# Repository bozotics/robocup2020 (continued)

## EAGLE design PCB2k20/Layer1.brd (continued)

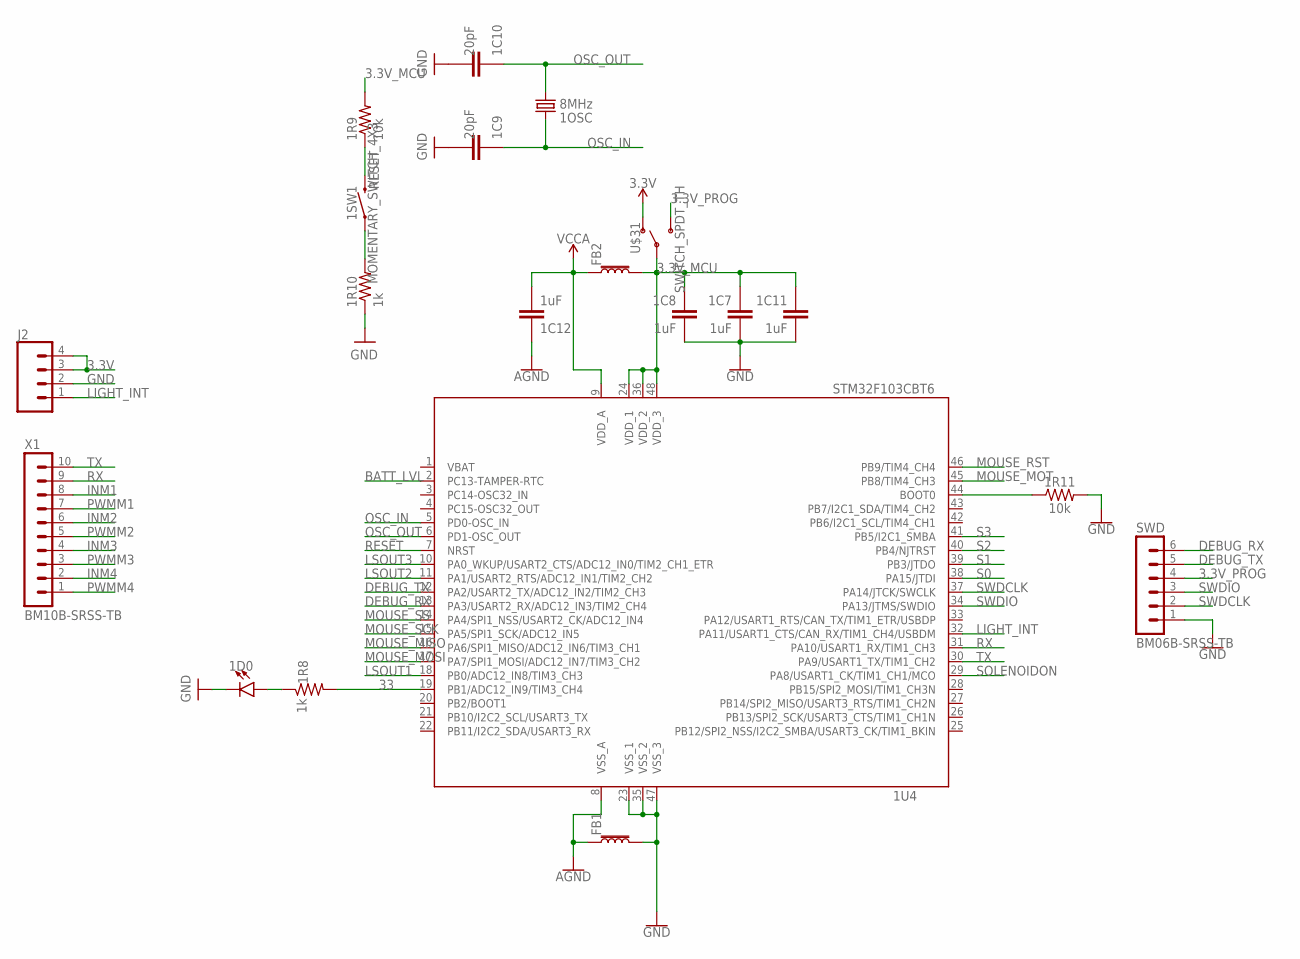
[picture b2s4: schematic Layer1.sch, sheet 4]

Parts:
1C7, 1C8, 1C11, 1C12: 1uF; C0603
1C9, 1C10: 20pF; C0603
1D0: BLUE; LED-0603
1OSC: 8MHz; CRYSTAL-SMD-5X3.2-2PAD
1R8, 1R10: 1k; R0603
1R9, 1R11: 10k; R0603
1SW1: MOMENTARY_SWITCH_4X3
1U4: STM32F103CBT6; LQFP48
FB1, FB2: FERRITE_BEAD; R0603
J2: CONN_04LOCK; 1X04_LOCK
SWD: BM06B-SRSS-TB
U$31: SWITCH_SPDT_TH; SWITCH_SPDT_PTH_11.6X4.0MM_LOCK
X1: BM10B-SRSS-TB

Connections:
3.3V: J2.3, J2.4, U$31.1 (O); also elsewhere on the board
3.3V_MCU: 1C7.1, 1C8.1, 1C11.1, 1R9.2, 1U4.24 (VDD_1), 1U4.36 (VDD_2), 1U4.48 (VDD_3), FB2.2, U$31.2
3.3V_PROG: SWD.4, U$31.3 (S)
33: 1R8.2, 1U4.19 (PB1/ADC12_IN9/TIM3_CH4)
AGND: 1C12.1, 1U4.8 (VSS_A), FB1.1; also elsewhere on the board
BATT_LVL: 1U4.2 (PC13-TAMPER-RTC); also elsewhere on the board
DEBUG_RX: 1U4.13 (PA3/USART2_RX/ADC12_IN3/TIM2_CH4), SWD.6
DEBUG_TX: 1U4.12 (PA2/USART2_TX/ADC12_IN2/TIM2_CH3), SWD.5
GND: 1C7.2, 1C8.2, 1C9.2, 1C10.2, 1C11.2, 1D0.C, 1R10.1, 1R11.2, 1U4.23 (VSS_1), 1U4.35 (VSS_2), 1U4.47 (VSS_3), FB1.2, J2.2, SWD.1; also elsewhere on the board
INM1: X1.8; also elsewhere on the board
INM2: X1.6; also elsewhere on the board
INM3: X1.4; also elsewhere on the board
INM4: X1.2; also elsewhere on the board
LIGHT_INT: 1U4.32 (PA11/USART1_CTS/CAN_RX/TIM1_CH4/USBDM), J2.1
LSOUT1: 1U4.18 (PB0/ADC12_IN8/TIM3_CH3); also elsewhere on the board
LSOUT2: 1U4.11 (PA1/USART2_RTS/ADC12_IN1/TIM2_CH2); also elsewhere on the board
LSOUT3: 1U4.10 (PA0_WKUP/USART2_CTS/ADC12_IN0/TIM2_CH1_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); also elsewhere on the board
MOUSE_MISO: 1U4.16 (PA6/SPI1_MISO/ADC12_IN6/TIM3_CH1); also elsewhere on the board
MOUSE_MOSI: 1U4.17 (PA7/SPI1_MOSI/ADC12_IN7/TIM3_CH2); also elsewhere on the board
MOUSE_MOT: 1U4.45 (PB8/TIM4_CH3); also elsewhere on the board
MOUSE_RST: 1U4.46 (PB9/TIM4_CH4); also elsewhere on the board
MOUSE_SCK: 1U4.15 (PA5/SPI1_SCK/ADC12_IN5); also elsewhere on the board
MOUSE_SS: 1U4.14 (PA4/SPI1_NSS/USART2_CK/ADC12_IN4); also elsewhere on the board
unnamed: 1R10.2, 1SW1.P$1 (1)
unnamed: 1D0.A, 1R8.1
unnamed: 1R11.1, 1U4.44 (BOOT0)
OSC_IN: 1C9.1, 1OSC.P$2 (2), 1U4.5 (PD0-OSC_IN)
OSC_OUT: 1C10.1, 1OSC.P$1 (1), 1U4.6 (PD1-OSC_OUT)
PWMM1: X1.7; also elsewhere on the board
PWMM2: X1.5; also elsewhere on the board
PWMM3: X1.3; also elsewhere on the board
PWMM4: X1.1; also elsewhere on the board
RESET: 1R9.1, 1SW1.P$2 (2), 1U4.7 (NRST)
RX: 1U4.31 (PA10/USART1_RX/TIM1_CH3), X1.9
S0: 1U4.38 (PA15/JTDI); also elsewhere on the board
S1: 1U4.39 (PB3/JTDO); also elsewhere on the board
S2: 1U4.40 (PB4/NJTRST); also elsewhere on the board
S3: 1U4.41 (PB5/I2C1_SMBA); also elsewhere on the board
SOLENOIDON: 1U4.29 (PA8/USART1_CK/TIM1_CH1/MCO); also elsewhere on the board
SWDCLK: 1U4.37 (PA14/JTCK/SWCLK), SWD.2
SWDIO: 1U4.34 (PA13/JTMS/SWDIO), SWD.3
TX: 1U4.30 (PA9/USART1_TX/TIM1_CH2), X1.10
VBAT: 1U4.1 (VBAT)
VCCA: 1C12.2, 1U4.9 (VDD_A), FB2.1; also elsewhere on the board

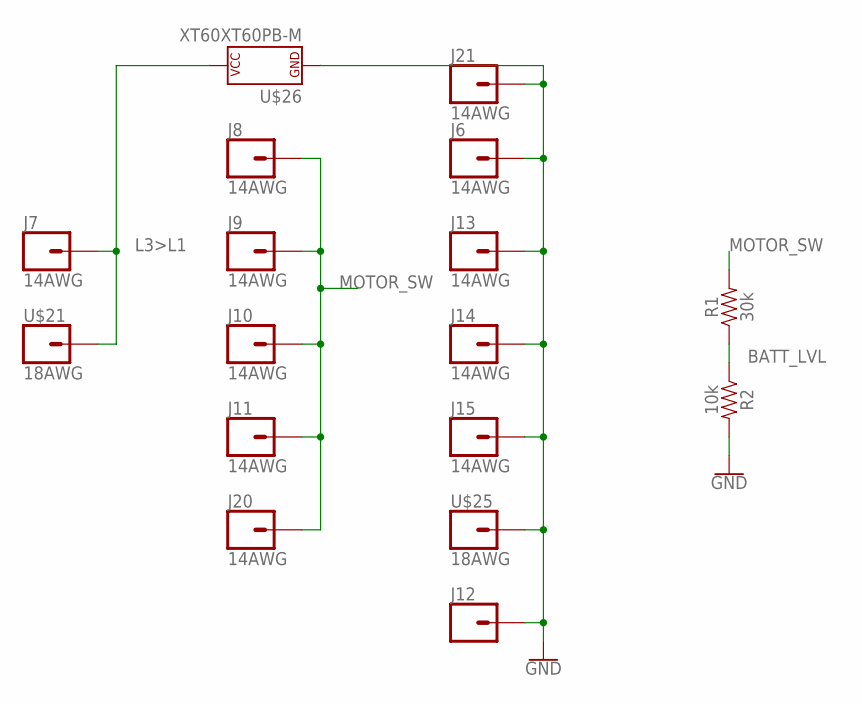
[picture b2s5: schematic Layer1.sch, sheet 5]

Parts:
J6, J7, J8, J9, J10, J11, J13, J14, J15, J20, J21: 14AWG
J12: CONN_01; 1X01
R1: 30k; R0603
R2: 10k; R0603
U$21, U$25: 18AWG
U$26: XT60XT60PB-M; XT60PB-M

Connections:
BATT_LVL: R1.1, R2.1; also elsewhere on the board
GND: J6.P$1, J12.1, J13.P$1, J14.P$1, J15.P$1, J21.P$1, R2.2, U$25.P$1, U$26.- (P$V-); also elsewhere on the board
L3>L1: J7.P$1, U$21.P$1, U$26.+ (P$V+)
MOTOR_SW: J8.P$1, J9.P$1, J10.P$1, J11.P$1, J20.P$1, R1.2

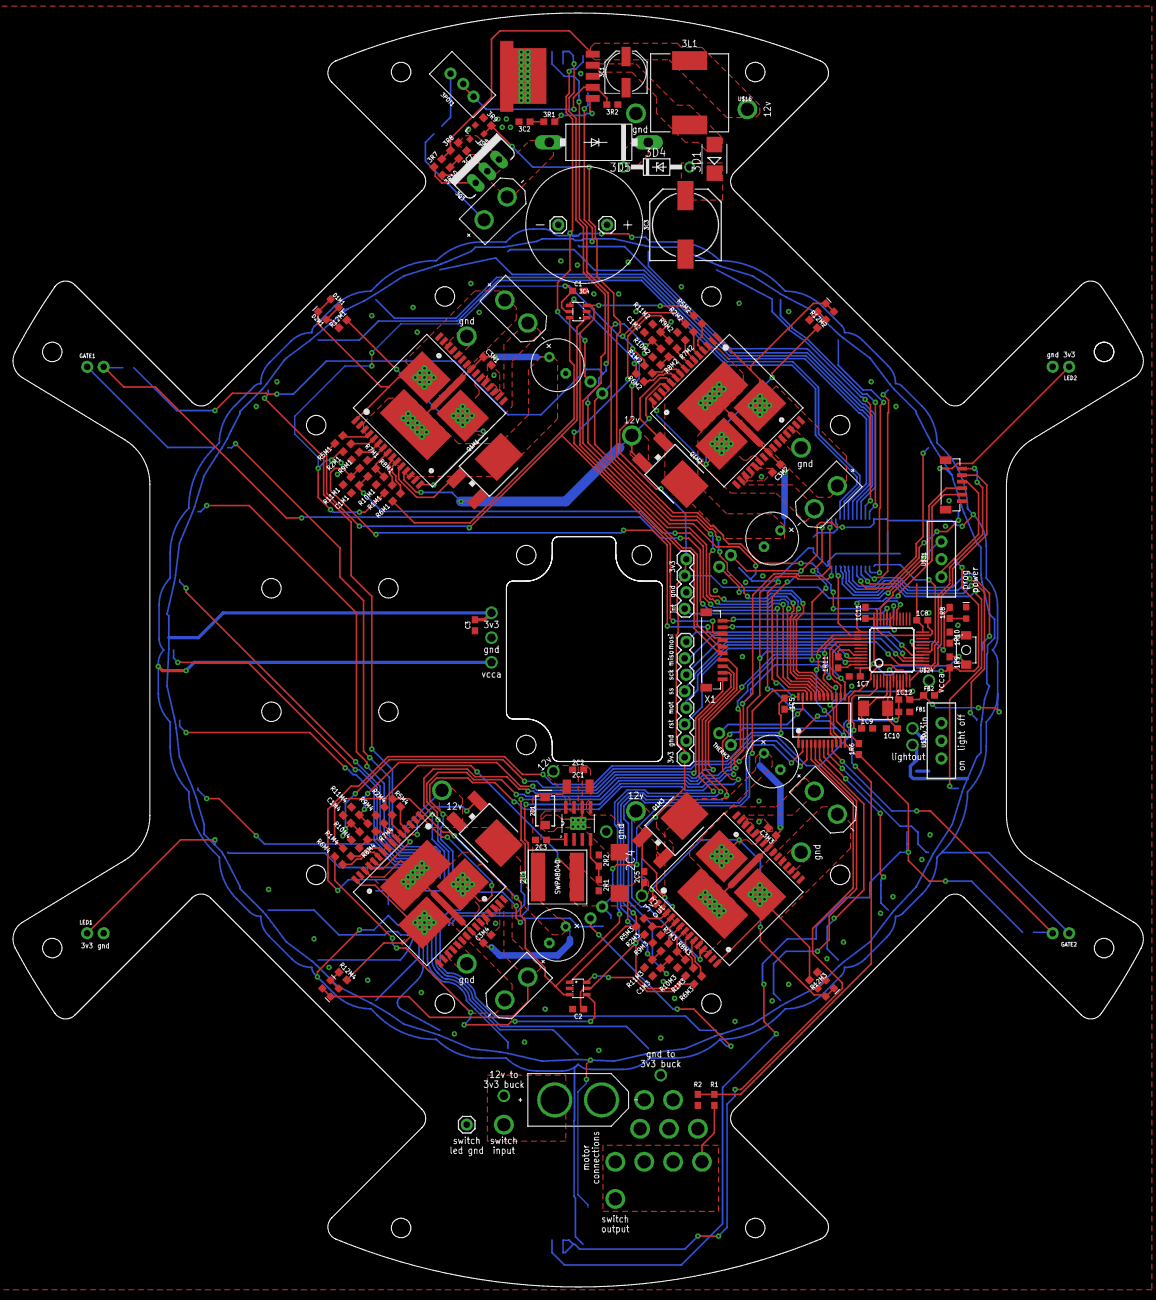
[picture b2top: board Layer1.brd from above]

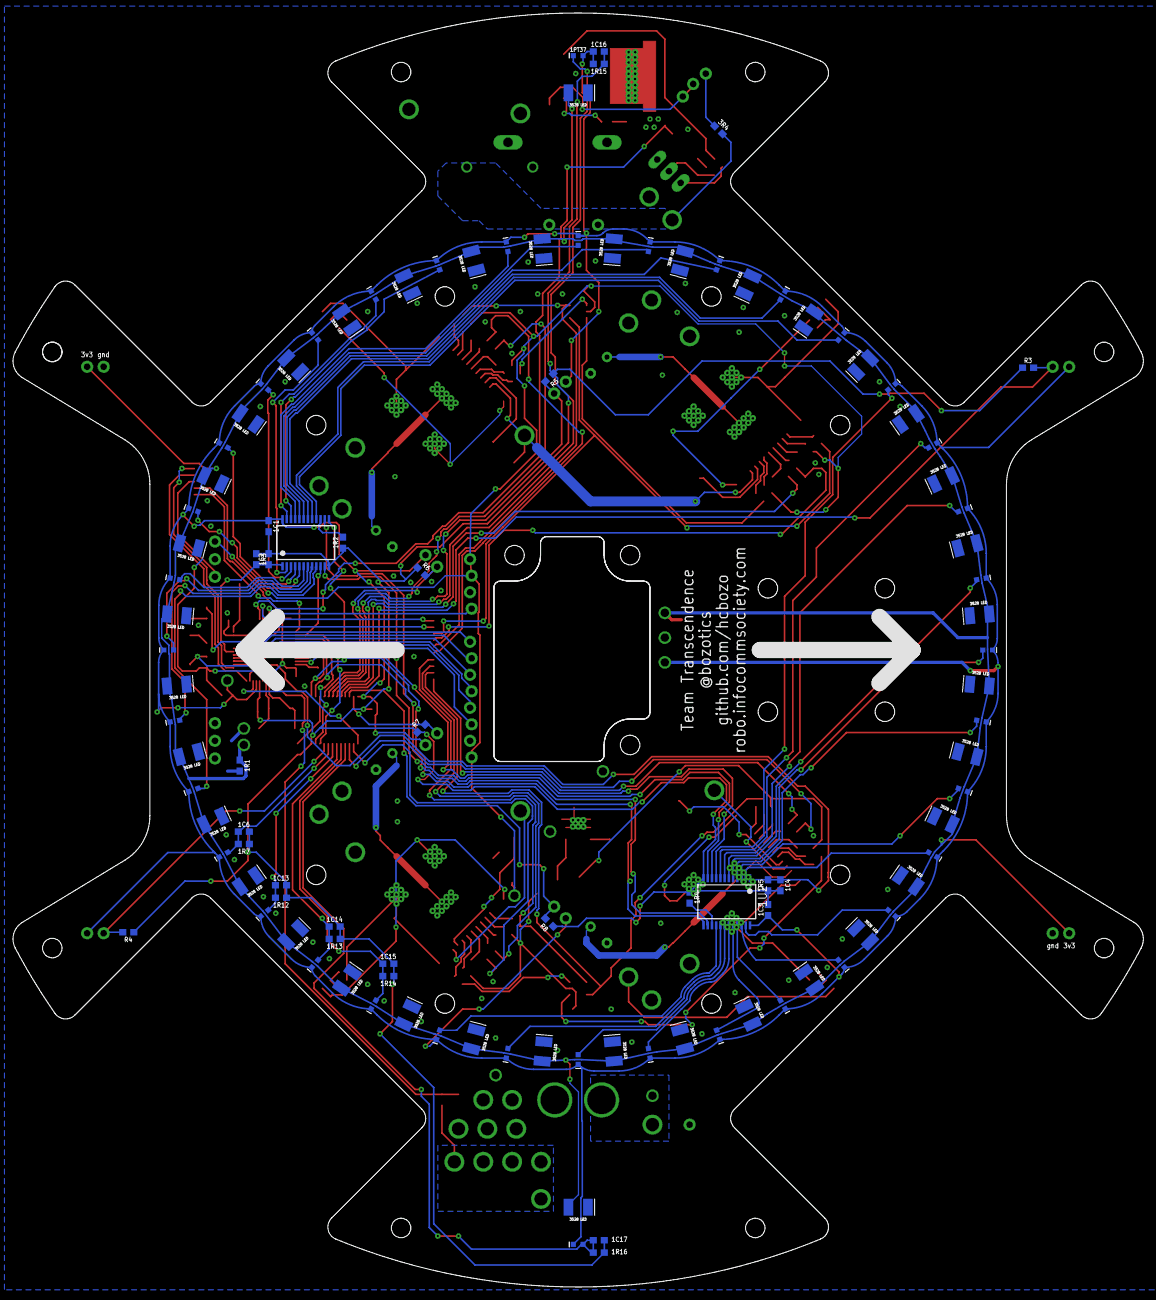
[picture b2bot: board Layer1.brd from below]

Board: 2 copper layers, 173.9 x 196.0 mm, 281 parts (106 on the bottom side), 170 nets.

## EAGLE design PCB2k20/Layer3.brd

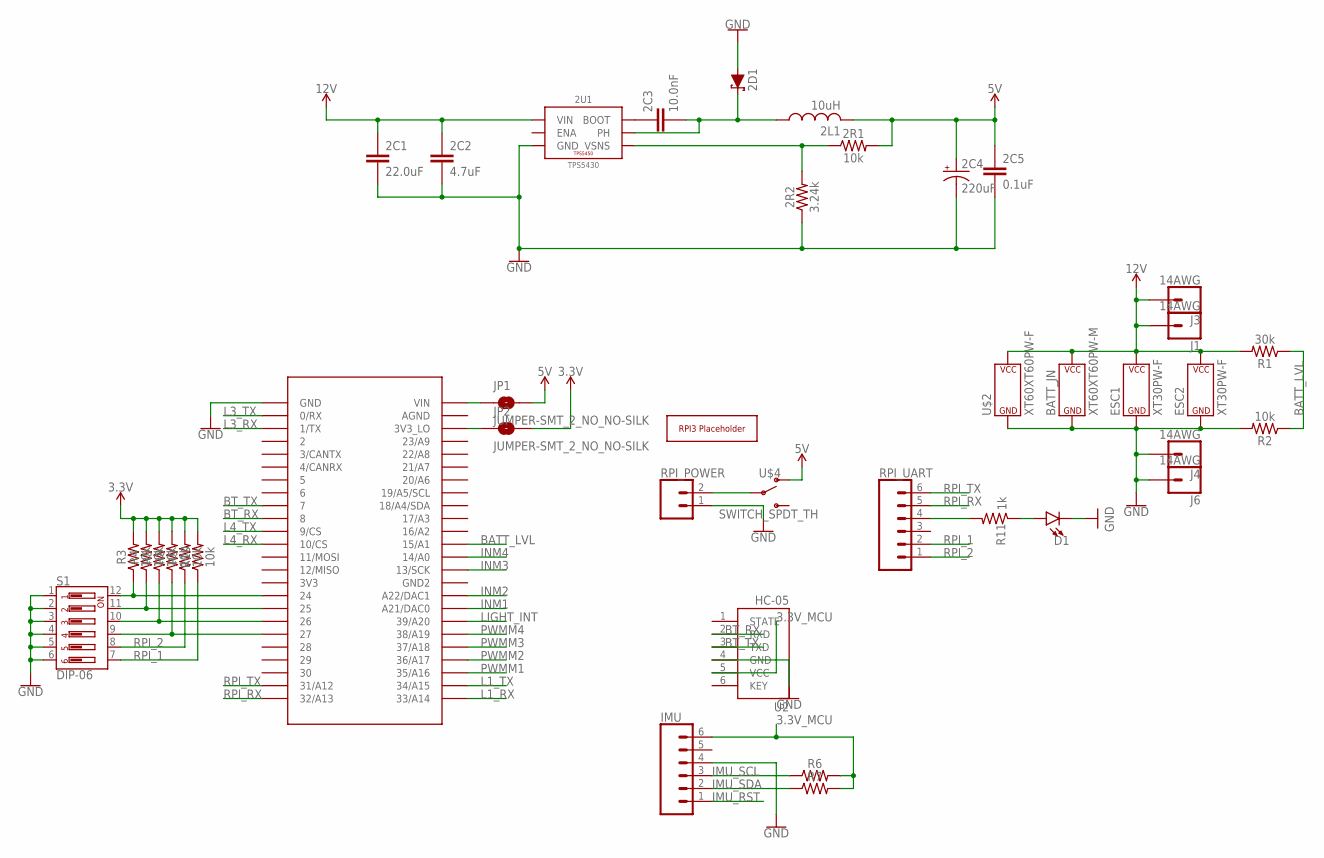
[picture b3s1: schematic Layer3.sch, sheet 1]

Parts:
2C1: 22.0uF; C1210
2C2: 4.7uF; C0603
2C3: 10.0nF; C0603
2C4: 220uF; D/7343-31R
2C5: 0.1uF; C0603
2D1: 3A/40V/500mV; SMA-DIODE
2L1: 10uH; SWPA8040
2R1: 10k; R0603
2R2: 3.24k; R0603
2U1: TPS5430; POWERPAD-SOIC-8
BATT_JN: XT60XT60PW-M; XT60PW-M
D1: BLUE; LED-0603
ESC1, ESC2: XT30PW-F
IMU: CONN_06FEMALE_LOCK; 1X06_FEMALE_LOCK.010
J1, J3, J4, J6: 14AWG
JP1, JP2: JUMPER-SMT_2_NO_NO-SILK; SMT-JUMPER_2_NO_NO-SILK
PCB1: RPI3
R1: 30k; R0603
R2, R3, R4, R5, R8, R9, R10: 10k; R0603
R6, R7: RESISTOR0603; R0603
R11: 1k; R0603
RPI_POWER: CONN_02LOCK; 1X02_LOCK
RPI_UART: CONN_06LOCK; 1X06_LOCK
S1: DIP-06; DIPSWITCH-06-SMD
U2: HC-05_BENT
U$1: TEENSY_3.5/3.6_NO_MIDDLE
U$2: XT60XT60PW-F; XT60PW-F
U$4: SWITCH_SPDT_TH; SWITCH_SPDT_PTH_11.6X4.0MM_LOCK

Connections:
3.3V: JP2.2, R3.2, R4.2, R5.2, R8.2, R9.2, R10.2; also elsewhere on the board
3.3V_MCU: IMU.6, R6.2, R7.2, U2.5 (VCC); also elsewhere on the board
5V: 2C4.+, 2C5.1, 2L1.P2 (2), 2R1.2, JP1.2, U$4.1 (O); also elsewhere on the board
12V: 2C1.1, 2C2.1, 2U1.7 (VIN), BATT_JN.+ (P$V+), ESC1.+ (P$V+), ESC2.+ (P$V+), J1.P$1, J3.P$1, R1.2, U$2.+ (P$V+)
BATT_LVL: R1.1, R2.1, U$1.15/A1
BT_RX: U2.2 (RXD), U$1.8
BT_TX: U2.3 (TXD), U$1.7
GND: 2C1.2, 2C2.2, 2C4.-, 2C5.2, 2D1.A, 2R2.1, 2U1.6 (GND), 2U1.9 (GND), 2U1.P$1 (GND), 2U1.P$2 (GND), 2U1.P$3 (GND), 2U1.P$4 (GND), 2U1.P$5 (GND), 2U1.P$6 (GND), BATT_JN.- (P$V-), D1.C, ESC1.- (P$V-), ESC2.- (P$V-), IMU.4, J4.P$1, J6.P$1, R2.2, RPI_POWER.1, S1.1, S1.2, S1.3, S1.4, S1.5, S1.6, U2.4 (GND), U$1.GND, U$2.- (P$V-); also elsewhere on the board
IMU_RST: IMU.1; also elsewhere on the board
IMU_SCL: IMU.3, R6.1; also elsewhere on the board
IMU_SDA: IMU.2, R7.1; also elsewhere on the board
INM1: U$1.A21/DAC0; also elsewhere on the board
INM2: U$1.A22/DAC1; also elsewhere on the board
INM3: U$1.13/SCK; also elsewhere on the board
INM4: U$1.14/A0; also elsewhere on the board
L1_RX: U$1.33/A14; also elsewhere on the board
L1_TX: U$1.34/A15; also elsewhere on the board
L3_RX: U$1.1/TX; also elsewhere on the board
L3_TX: U$1.0/RX; also elsewhere on the board
L4_RX: U$1.10/CS; also elsewhere on the board
L4_TX: U$1.9/CS; also elsewhere on the board
LIGHT_INT: U$1.39/A20; also elsewhere on the board
unnamed: JP1.1, U$1.VIN
unnamed: JP2.1, U$1.3V3_LO
unnamed: R4.1, S1.11, U$1.25
unnamed: 2C3.2, 2D1.C, 2L1.P1 (1), 2U1.8 (PH)
unnamed: 2R1.1, 2R2.2, 2U1.4 (VSNS)
unnamed: 2C3.1, 2U1.1 (BOOT)
unnamed: RPI_POWER.2, U$4.2
unnamed: R3.1, S1.12, U$1.24
unnamed: R5.1, S1.10, U$1.26
unnamed: R8.1, S1.9, U$1.27
unnamed: R11.2, RPI_UART.4
unnamed: D1.A, R11.1
PWMM1: U$1.35/A16; also elsewhere on the board
PWMM2: U$1.36/A17; also elsewhere on the board
PWMM3: U$1.37/A18; also elsewhere on the board
PWMM4: U$1.38/A19; also elsewhere on the board
RPI_1: R10.1, RPI_UART.2, S1.7
RPI_2: R9.1, RPI_UART.1, S1.8
RPI_RX: RPI_UART.5, U$1.32/A13
RPI_TX: RPI_UART.6, U$1.31/A12

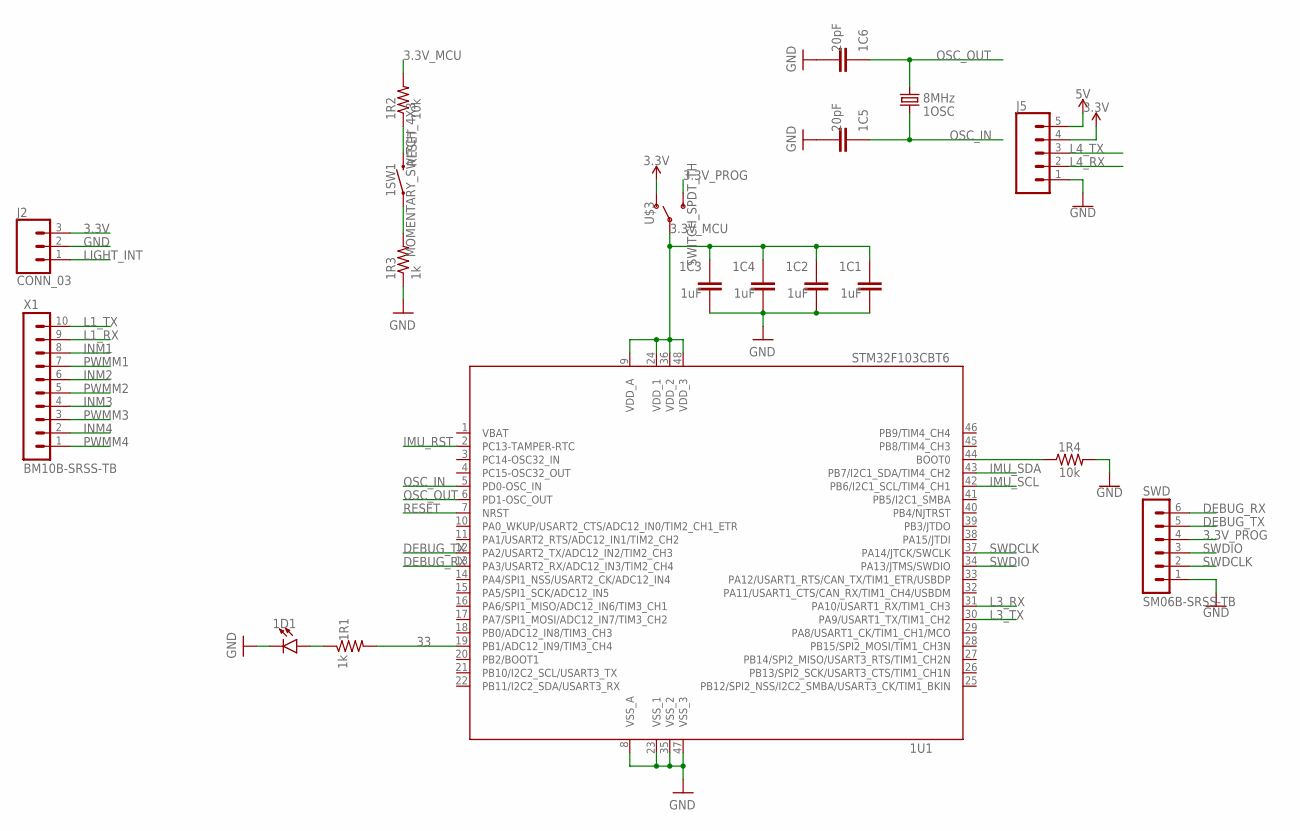
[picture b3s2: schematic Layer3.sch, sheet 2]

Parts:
1C1, 1C2, 1C3, 1C4: 1uF; C0603
1C5, 1C6: 20pF; C0603
1D1: BLUE; LED-0603
1OSC: 8MHz; CRYSTAL-SMD-5X3.2-2PAD
1R1, 1R3: 1k; R0603
1R2, 1R4: 10k; R0603
1SW1: MOMENTARY_SWITCH_4X3
1U1: STM32F103CBT6; LQFP48
J2: CONN_03; 1X03_LOCK
J5: CONN_05LOCK; 1X05_LOCK
SWD: SM06B-SRSS-TB
U$3: SWITCH_SPDT_TH; SWITCH_SPDT_PTH_11.6X4.0MM_LOCK
X1: BM10B-SRSS-TB

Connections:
3.3V: J2.3, J5.4, U$3.1 (O); also elsewhere on the board
3.3V_MCU: 1C1.1, 1C2.1, 1C3.1, 1C4.1, 1R2.2, 1U1.9 (VDD_A), 1U1.24 (VDD_1), 1U1.36 (VDD_2), 1U1.48 (VDD_3), U$3.2; also elsewhere on the board
3.3V_PROG: SWD.4, U$3.3 (S)
5V: J5.5; also elsewhere on the board
33: 1R1.2, 1U1.19 (PB1/ADC12_IN9/TIM3_CH4)
DEBUG_RX: 1U1.13 (PA3/USART2_RX/ADC12_IN3/TIM2_CH4), SWD.6
DEBUG_TX: 1U1.12 (PA2/USART2_TX/ADC12_IN2/TIM2_CH3), SWD.5
GND: 1C1.2, 1C2.2, 1C3.2, 1C4.2, 1C5.2, 1C6.2, 1D1.C, 1R3.1, 1R4.2, 1U1.8 (VSS_A), 1U1.23 (VSS_1), 1U1.35 (VSS_2), 1U1.47 (VSS_3), J2.2, J5.1, SWD.1; also elsewhere on the board
IMU_RST: 1U1.2 (PC13-TAMPER-RTC); also elsewhere on the board
IMU_SCL: 1U1.42 (PB6/I2C1_SCL/TIM4_CH1); also elsewhere on the board
IMU_SDA: 1U1.43 (PB7/I2C1_SDA/TIM4_CH2); also elsewhere on the board
INM1: X1.8; also elsewhere on the board
INM2: X1.6; also elsewhere on the board
INM3: X1.4; also elsewhere on the board
INM4: X1.2; also elsewhere on the board
L1_RX: X1.9; also elsewhere on the board
L1_TX: X1.10; also elsewhere on the board
L3_RX: 1U1.31 (PA10/USART1_RX/TIM1_CH3); also elsewhere on the board
L3_TX: 1U1.30 (PA9/USART1_TX/TIM1_CH2); also elsewhere on the board
L4_RX: J5.2; also elsewhere on the board
L4_TX: J5.3; also elsewhere on the board
LIGHT_INT: J2.1; also elsewhere on the board
unnamed: 1D1.A, 1R1.1
unnamed: 1R3.2, 1SW1.P$1 (1)
unnamed: 1R4.1, 1U1.44 (BOOT0)
OSC_IN: 1C5.1, 1OSC.P$2 (2), 1U1.5 (PD0-OSC_IN)
OSC_OUT: 1C6.1, 1OSC.P$1 (1), 1U1.6 (PD1-OSC_OUT)
PWMM1: X1.7; also elsewhere on the board
PWMM2: X1.5; also elsewhere on the board
PWMM3: X1.3; also elsewhere on the board
PWMM4: X1.1; also elsewhere on the board
RESET: 1R2.1, 1SW1.P$2 (2), 1U1.7 (NRST)
SWDCLK: 1U1.37 (PA14/JTCK/SWCLK), SWD.2
SWDIO: 1U1.34 (PA13/JTMS/SWDIO), SWD.3
VBAT: 1U1.1 (VBAT)

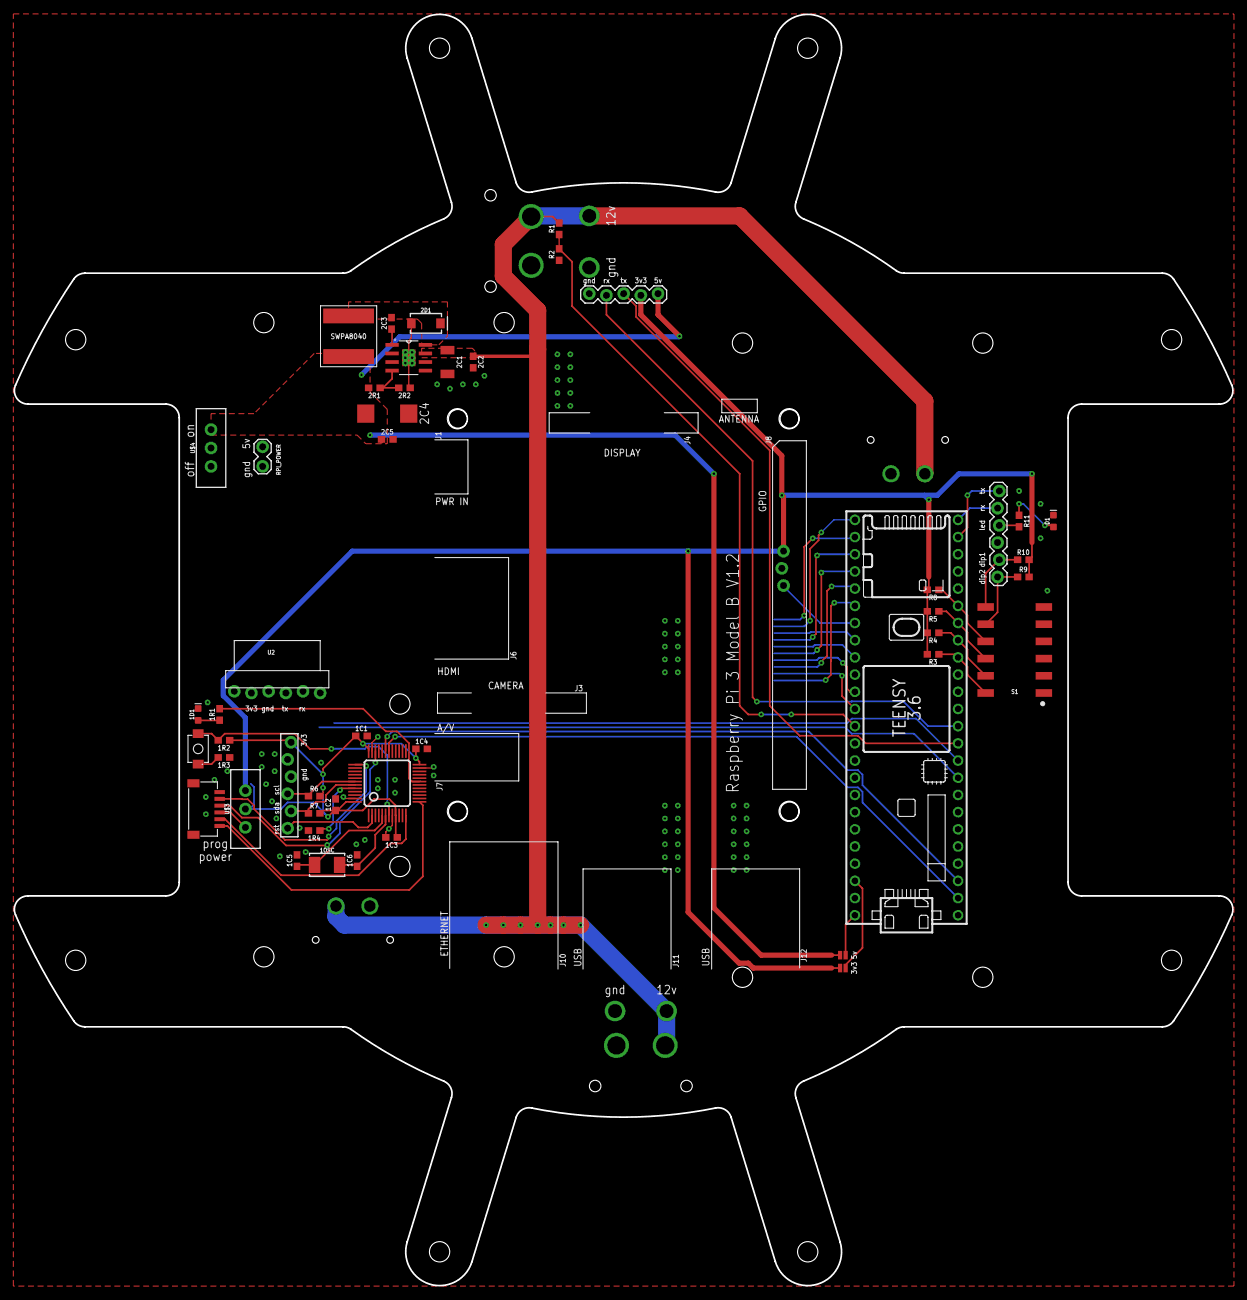
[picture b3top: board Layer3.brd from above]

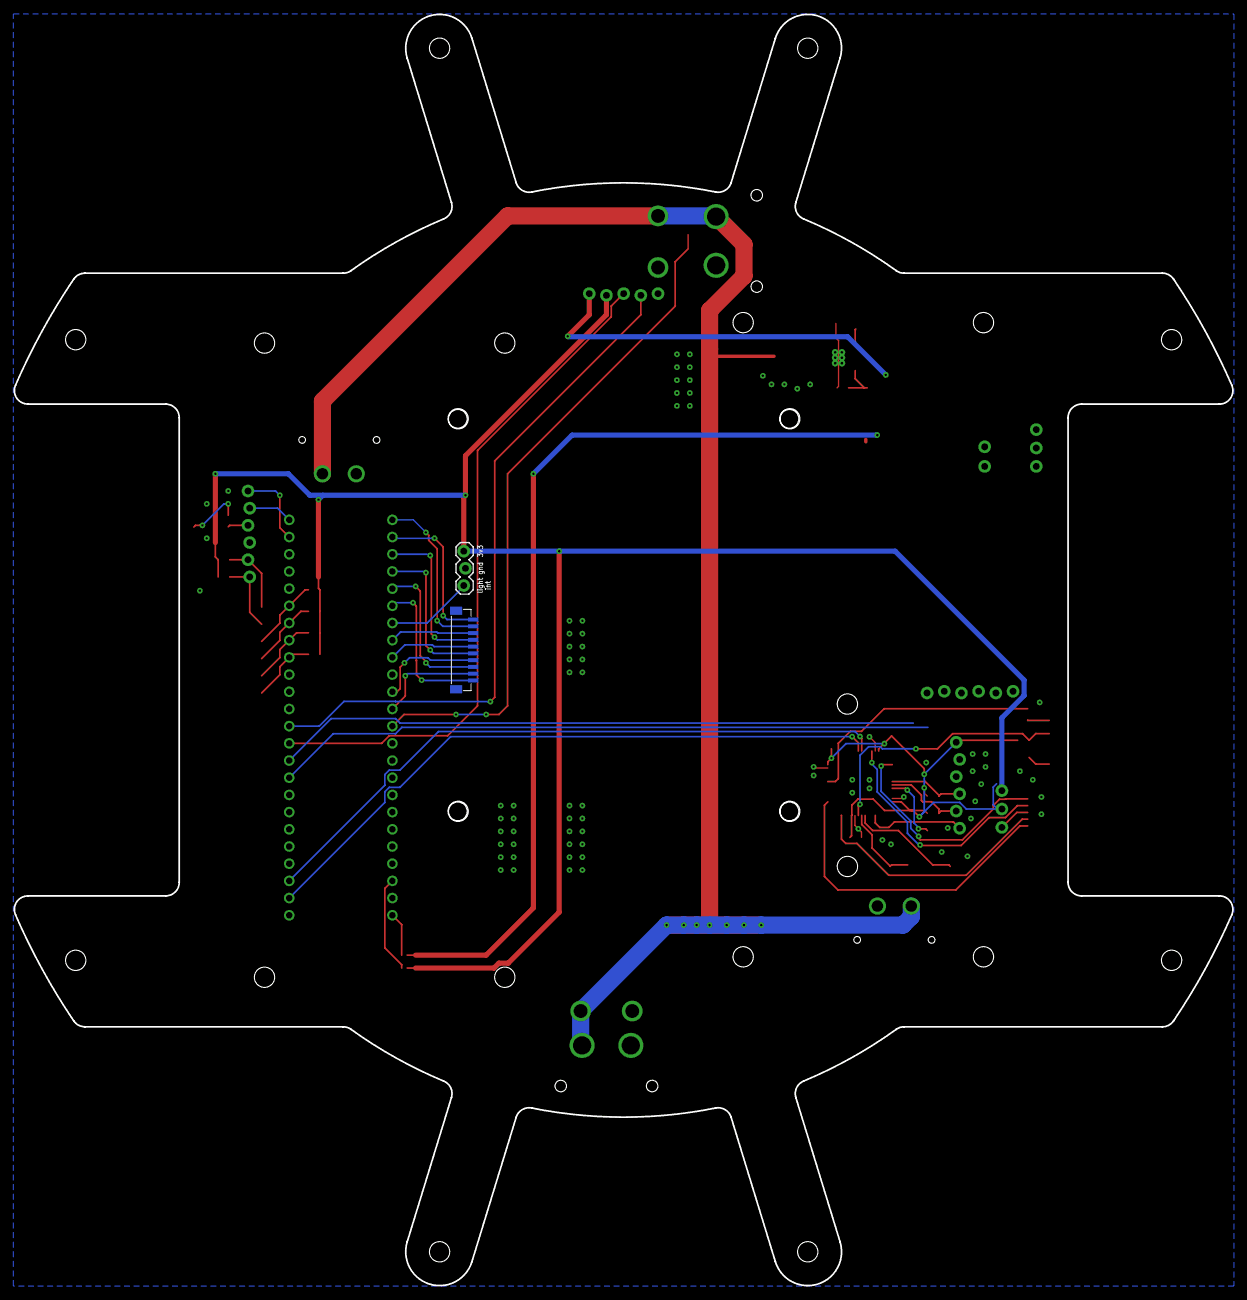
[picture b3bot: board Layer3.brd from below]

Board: 2 copper layers, 180.0 x 187.8 mm, 59 parts (2 on the bottom side), 54 nets.

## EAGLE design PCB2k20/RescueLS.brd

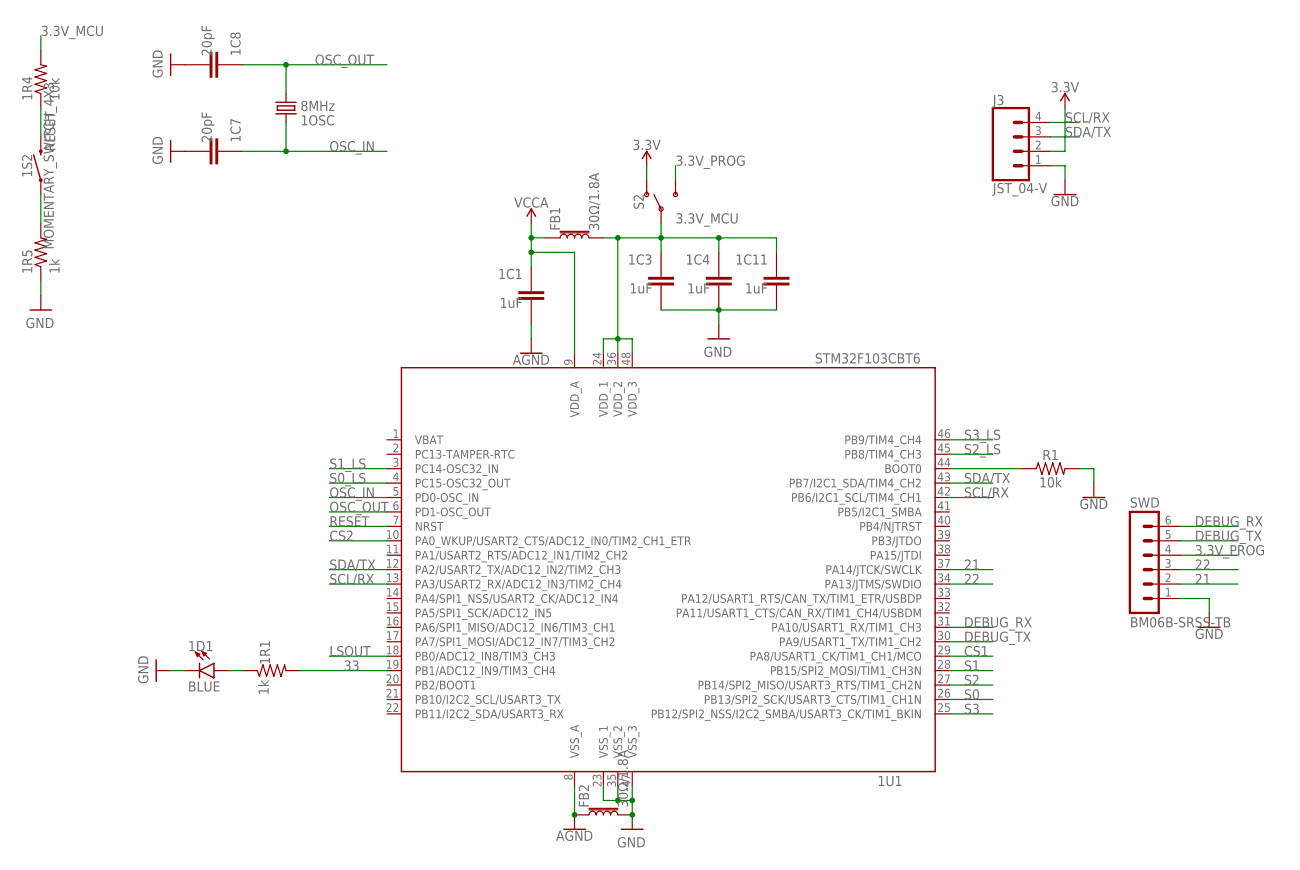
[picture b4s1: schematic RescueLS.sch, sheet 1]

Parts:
1C1, 1C3, 1C4, 1C11: 1uF; C0603
1C7, 1C8: 20pF; C0603
1D1: BLUE; LED-0603
1OSC: 8MHz; CRYSTAL-SMD-5X3.2-2PAD
1R1, 1R5: 1k; R0603
1R4: 10k; R0603
1S2: MOMENTARY_SWITCH_4X3
1U1: STM32F103CBT6; LQFP48
FB1, FB2: 30Ω/1.8A; 0603
J3: JST_04-V
R1: 10k; R0603
S2: SWITCH-SPDT-PTH-11.6X4.0MM-LOCK; SWITCH_SPDT_PTH_11.6X4.0MM_LOCK
SWD: BM06B-SRSS-TB

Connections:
3.3V: J3.2, S2.1 (O); also elsewhere on the board
3.3V_MCU: 1C3.1, 1C4.1, 1C11.1, 1R4.2, 1U1.24 (VDD_1), 1U1.36 (VDD_2), 1U1.48 (VDD_3), FB1.2, S2.2; also elsewhere on the board
3.3V_PROG: S2.3 (S), SWD.4
21: 1U1.37 (PA14/JTCK/SWCLK), SWD.2
22: 1U1.34 (PA13/JTMS/SWDIO), SWD.3
33: 1R1.2, 1U1.19 (PB1/ADC12_IN9/TIM3_CH4)
AGND: 1C1.2, 1U1.8 (VSS_A), FB2.1; also elsewhere on the board
CS1: 1U1.29 (PA8/USART1_CK/TIM1_CH1/MCO); also elsewhere on the board
CS2: 1U1.10 (PA0_WKUP/USART2_CTS/ADC12_IN0/TIM2_CH1_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); also elsewhere on the board
DEBUG_RX: 1U1.31 (PA10/USART1_RX/TIM1_CH3), SWD.6
DEBUG_TX: 1U1.30 (PA9/USART1_TX/TIM1_CH2), SWD.5
GND: 1C3.2, 1C4.2, 1C7.2, 1C8.2, 1C11.2, 1D1.C, 1R5.1, 1U1.23 (VSS_1), 1U1.35 (VSS_2), 1U1.47 (VSS_3), FB2.2, J3.1, R1.2, SWD.1; also elsewhere on the board
LSOUT: 1U1.18 (PB0/ADC12_IN8/TIM3_CH3); also elsewhere on the board
unnamed: 1D1.A, 1R1.1
unnamed: 1R5.2, 1S2.P$1 (1)
unnamed: 1U1.44 (BOOT0), R1.1
OSC_IN: 1C7.1, 1OSC.P$2 (2), 1U1.5 (PD0-OSC_IN)
OSC_OUT: 1C8.1, 1OSC.P$1 (1), 1U1.6 (PD1-OSC_OUT)
RESET: 1R4.1, 1S2.P$2 (2), 1U1.7 (NRST)
S0: 1U1.26 (PB13/SPI2_SCK/USART3_CTS/TIM1_CH1N); also elsewhere on the board
S0_LS: 1U1.4 (PC15-OSC32_OUT); also elsewhere on the board
S1: 1U1.28 (PB15/SPI2_MOSI/TIM1_CH3N); also elsewhere on the board
S1_LS: 1U1.3 (PC14-OSC32_IN); also elsewhere on the board
S2: 1U1.27 (PB14/SPI2_MISO/USART3_RTS/TIM1_CH2N); also elsewhere on the board
S2_LS: 1U1.45 (PB8/TIM4_CH3); also elsewhere on the board
S3: 1U1.25 (PB12/SPI2_NSS/I2C2_SMBA/USART3_CK/TIM1_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); also elsewhere on the board
S3_LS: 1U1.46 (PB9/TIM4_CH4); also elsewhere on the board
SCL/RX: 1U1.13 (PA3/USART2_RX/ADC12_IN3/TIM2_CH4), 1U1.42 (PB6/I2C1_SCL/TIM4_CH1), J3.4
SDA/TX: 1U1.12 (PA2/USART2_TX/ADC12_IN2/TIM2_CH3), 1U1.43 (PB7/I2C1_SDA/TIM4_CH2), J3.3
VBAT: 1U1.1 (VBAT)
VCCA: 1C1.1, 1U1.9 (VDD_A), FB1.1; also elsewhere on the board

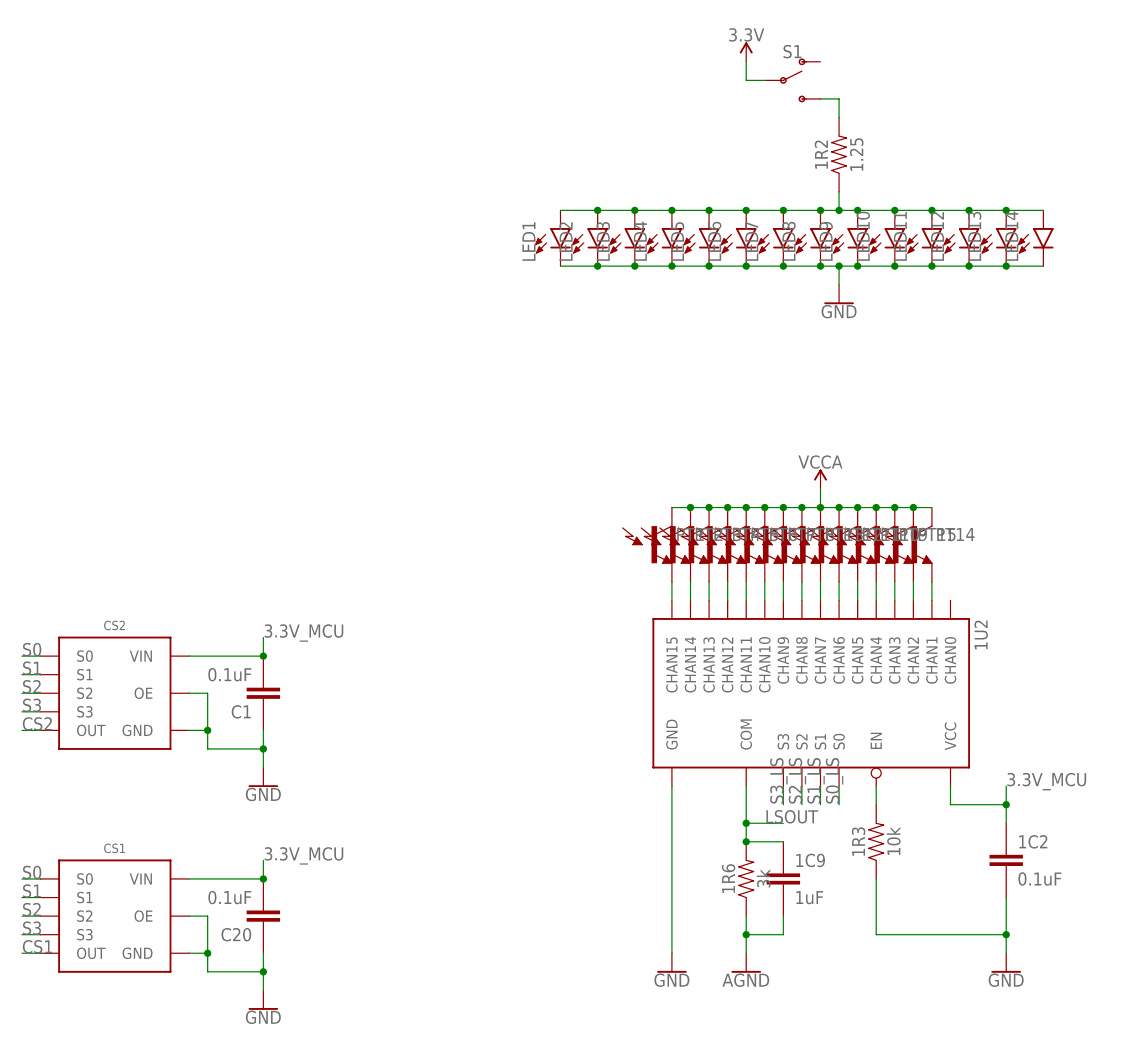
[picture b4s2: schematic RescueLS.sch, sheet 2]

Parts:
1C2: 0.1uF; C0603
1C9: 1uF; C0603
1R2: 1.25; R0603
1R3: 10k; R0603
1R6: 3k; R0603
1U2: 74HC4067; SOIC-24
C1, C20: 0.1uF; C0603
CS1, CS2: TCS3200; SOIC-8
LED1, LED2, LED3, LED4, LED5, LED6, LED7, LED8, LED9, LED10, LED11, LED12, LED13, LED14: 3528LED; 3528
PT1, PT2, PT3, PT4, PT5, PT6, PT7, PT8, PT9, PT10, PT11, PT12, PT13, PT14, PT15: LIGHT_SENSORALS; ALS-PT19
S1: SWITCH-SPDT-PTH-11.6X4.0MM-LOCK; SWITCH_SPDT_PTH_11.6X4.0MM_LOCK

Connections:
3.3V: S1.2; also elsewhere on the board
3.3V_MCU: 1C2.1, 1U2.P24 (VCC), C1.2, C20.2, CS1.5 (VIN), CS2.5 (VIN); also elsewhere on the board
AGND: 1C9.2, 1R6.1; also elsewhere on the board
CS1: CS1.6 (OUT); also elsewhere on the board
CS2: CS2.6 (OUT); also elsewhere on the board
GND: 1C2.2, 1R3.1, 1U2.P12 (GND), C1.1, C20.1, CS1.3 (OE), CS1.4 (GND), CS2.3 (OE), CS2.4 (GND), LED1.C, LED2.C, LED3.C, LED4.C, LED5.C, LED6.C, LED7.C, LED8.C, LED9.C, LED10.C, LED11.C, LED12.C, LED13.C, LED14.C; also elsewhere on the board
LSOUT: 1C9.1, 1R6.2, 1U2.P1 (COM); also elsewhere on the board
unnamed: 1U2.P8 (CHAN1), PT14.E (E1)
unnamed: 1R2.1, LED1.A, LED2.A, LED3.A, LED4.A, LED5.A, LED6.A, LED7.A, LED8.A, LED9.A, LED10.A, LED11.A, LED12.A, LED13.A, LED14.A
unnamed: 1R2.2, S1.3 (S)
unnamed: 1U2.P6 (CHAN3), PT9.E (E1)
unnamed: 1U2.P5 (CHAN4), PT10.E (E1)
unnamed: 1U2.P4 (CHAN5), PT11.E (E1)
unnamed: 1U2.P3 (CHAN6), PT12.E (E1)
unnamed: 1U2.P2 (CHAN7), PT13.E (E1)
unnamed: 1U2.P7 (CHAN2), PT15.E (E1)
unnamed: 1R3.2, 1U2.P15 (EN)
unnamed: 1U2.P16 (CHAN15), PT1.E (E1)
unnamed: 1U2.P17 (CHAN14), PT2.E (E1)
unnamed: 1U2.P18 (CHAN13), PT3.E (E1)
unnamed: 1U2.P19 (CHAN12), PT4.E (E1)
unnamed: 1U2.P20 (CHAN11), PT5.E (E1)
unnamed: 1U2.P21 (CHAN10), PT6.E (E1)
unnamed: 1U2.P22 (CHAN9), PT7.E (E1)
unnamed: 1U2.P23 (CHAN8), PT8.E (E1)
S0: CS1.1 (S0), CS2.1 (S0); also elsewhere on the board
S0_LS: 1U2.P10 (S0); also elsewhere on the board
S1: CS1.2 (S1), CS2.2 (S1); also elsewhere on the board
S1_LS: 1U2.P11 (S1); also elsewhere on the board
S2: CS1.7 (S2), CS2.7 (S2); also elsewhere on the board
S2_LS: 1U2.P14 (S2); also elsewhere on the board
S3: CS1.8 (S3), CS2.8 (S3); also elsewhere on the board
S3_LS: 1U2.P13 (S3); also elsewhere on the board
VCCA: PT1.C (C1), PT2.C (C1), PT3.C (C1), PT4.C (C1), PT5.C (C1), PT6.C (C1), PT7.C (C1), PT8.C (C1), PT9.C (C1), PT10.C (C1), PT11.C (C1), PT12.C (C1), PT13.C (C1), PT14.C (C1), PT15.C (C1); also elsewhere on the board

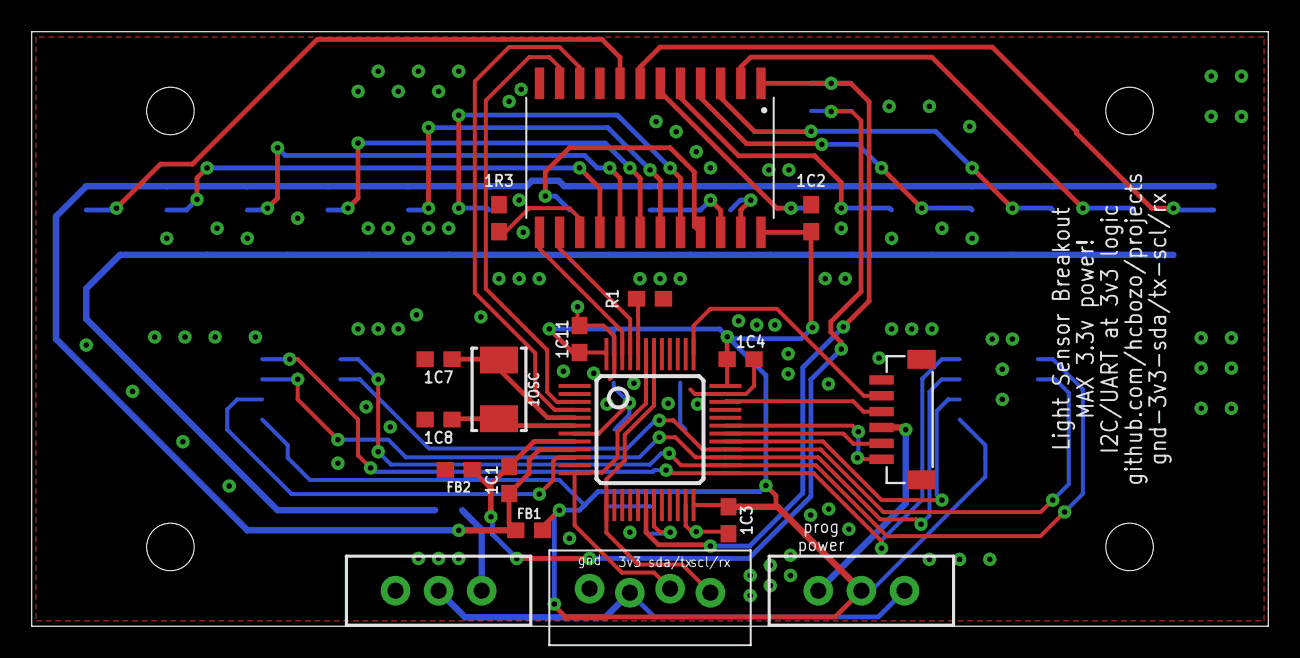
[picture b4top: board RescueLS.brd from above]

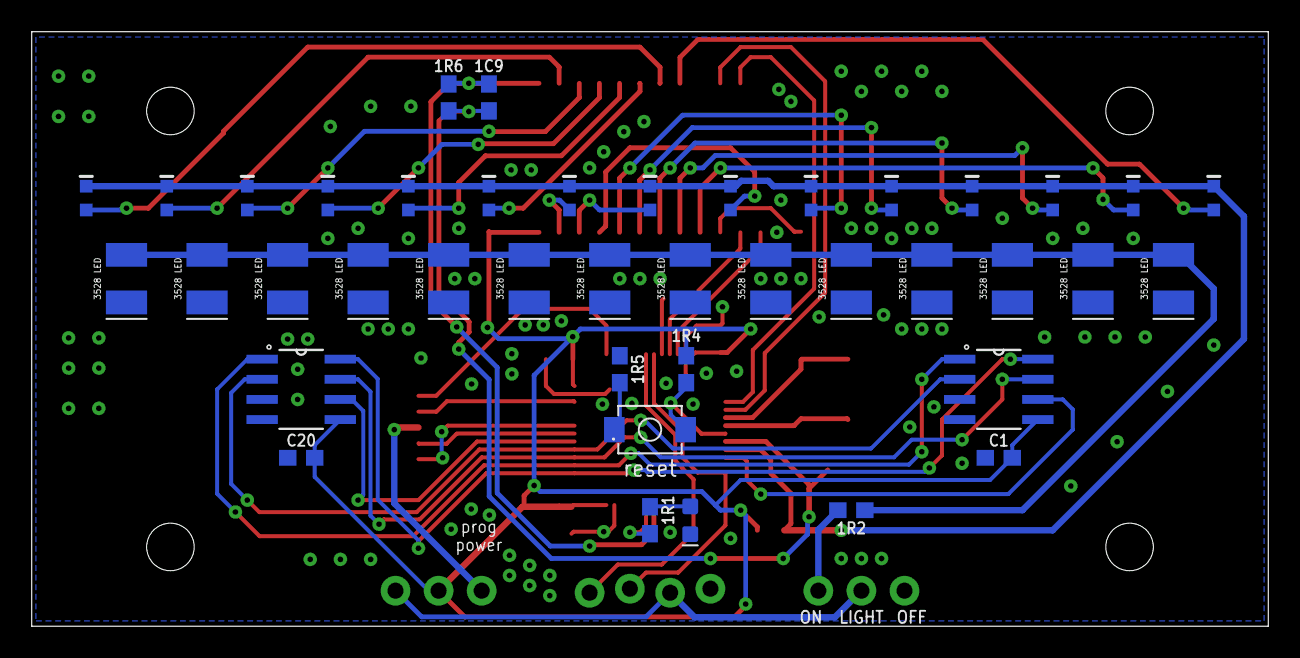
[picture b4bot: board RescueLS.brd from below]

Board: 2 copper layers, 78.0 x 37.5 mm, 59 parts (41 on the bottom side), 48 nets.
